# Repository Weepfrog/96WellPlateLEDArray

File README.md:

# 12×8 High-Power 660nm LED Array

A 96-LED (12 across × 8 down, 9 mm pitch) deep-red 660 nm panel with **per-LED
dimming** and **per-LED temperature sensing**, driven by an ESP32 DevKitC.
Designed for JLCPCB fabrication + assembly; all parts chosen from the
JLCPCB/LCSC library (stock verified 2026-07-13).

## System overview

```
24V 4-6A brick ──► CONTROL BOARD ══ 4× 50-way + 1× 20-way IDC ribbon ══► LED BOARD
                   96× PT4115 buck CC        192 anode/cathode lines        96× 660nm 3535 LED
                   6× PCA9685 PWM (I2C)      + analog/logic lines           96× 10k NTC
                   XL1509 5V rail                                           6× CD74HC4067 mux
                   ESP32 DevKitC socket                                     flat back → heatsink
                   3 buttons + status LEDs
```

- **~50 W** total at full drive (≈0.5 W per LED @ 256 mA, huge margin on 3 W-rated LEDs)
- Per-LED PWM: one PT4115 buck constant-current channel per LED, DIM pins on six
  PCA9685 16-channel I2C PWM expanders (run PWM at ~244 Hz → ~10-11 usable bits)
- Per-LED temperature: one 0603 NTC beside each LED, multiplexed 16:1 onto six
  ESP32 ADC1 inputs
- LED board is 4-layer with thermal-via farms; back face is bare copper for a
  bolt-on heatsink (use an insulating thermal pad)

## Repository layout

| Path | What |
|---|---|
| `12x8 Led Array 9mm pitch/` | **LED board** KiCad project (96 LEDs + NTCs + muxes) |
| `control-board/` | **Control board** KiCad project (drivers, PWM, ESP32, UI) |
| `libraries/` | `jlc_parts` symbol/footprint/3D library (converted from EasyEDA, JLCPCB-exact pads) |
| `scripts/design_data.py` | **Single source of truth**: every part, position, and net |
| `scripts/gen_schematics.py` | Regenerates both `.kicad_sch` (parts placed, you wire per CONNECTIONS.md) |
| `scripts/gen_pcbs.py` | Regenerates both `.kicad_pcb` (footprints pre-placed) |
| `reference/datasheets/` | Datasheets for key parts |
| `production/` | JLCPCB BOM + CPL exports |
| `CONNECTIONS.md` | **Your wiring guide** — every net, pin by pin |

## Workflow

1. **Schematics are hierarchical and fully wired**: each board is a root
   sheet + one sub-sheet (`well.kicad_sch` / `channel.kicad_sch`)
   instantiated 96×, with references matching `CONNECTIONS.md` (LED1-96,
   U1-96, …). Verified automatically: KiCad's exported netlist matches the
   intended netlist in `design_data.py` net-for-net; ERC is clean (3 benign
   library-mismatch warnings on the control board). Review, then move to
   layout.
2. Open the PCB — footprints are pre-placed (LED grid at exact 9.0 mm
   pitch; placement still draft). Run **Tools → Update PCB from Schematic
   (F8)**, then route.
3. Regenerating: `python scripts/gen_schematics_hier.py`, then
   `scripts/gen_pcbs.py` with KiCad's Python (see script headers), then
   `python scripts/gen_connections.py`. Verify with
   `scripts/verify_netlist.py` (see header). **Regeneration overwrites the
   sch/pcb files** — don't rerun after manual edits unless you want a reset.

## Key design rules (don't skip)

- **LED polarity:** pad 1 = anode (marked `+` on silk), pad 2 = cathode,
  pad 3 = center thermal pad — **tie pad 3 to pad 2 (cathode)** per Hongli's
  datasheet. Each LED's thermal island is at its own cathode potential, so the
  heatsink must be electrically isolated (thermal pad, not bare paste).
- **PT4115 DIM floats high** = full brightness. Every DIM has a 100k pulldown
  so the panel boots dark. Keep them.
- **One reflow only** for the LEDs (datasheet) — LED board is single-side
  assembly, which satisfies this. Don't hot-air rework casually.
- 24 V power enters each board via its own screw terminal — **do not route
  LED supply current through the IDC ribbons** (they carry per-channel
  anode/cathode pairs and logic only).
- IDC headers and ESP32 sockets are through-hole: hand-solder them (cheaper
  than JLCPCB THT assembly).

## Swapping LED wavelengths

The design is wavelength-agnostic on purpose:

- The 3535 3-pad footprint is the industry-standard pattern (Cree XP
  compatible). 730 nm far-red, 850/940 nm IR, blue, and UV parts from Hongli,
  Silverlight, JNJ and others drop straight in.
- The PT4115 buck **does not care about forward voltage** — anything from
  ~1.5 V (IR) to ~3.4 V (blue/UV) runs at the same regulated current with zero
  component changes.
- Current is set only by the 0.39 Ω sense resistor (256 mA). For a lower-rated
  LED, change R1–R96 on the control board: `I = 0.1 V / Rs`.
- Checklist when swapping: 3535 package with center pad, anode on pad 1 /
  matching polarity, continuous current rating ≥ 300 mA, note the part's own
  reflow limits.
- Mixed arrays are fine too (e.g. 660 nm + 730 nm checkerboard) since every
  channel is independent.

## Firmware map (ESP32 DevKitC-38)

| GPIO | Function |
|---|---|
| 21 / 22 | I2C SDA / SCL → PCA9685 ×6 (0x40–0x45), optional ADS1115 (0x48) |
| 16 / 17 / 18 / 19 | Mux address S0–S3 (shared, all six muxes) |
| 32, 33, 34, 35, 36, 39 | ADC1 inputs ← NTC_SIG1–6 (mux outputs) |
| 25 | Fan PWM (low-side AO3400A) |
| 4 / 13 | Status LED (blue) / Fault LED (red) |
| 14 / 27 / 26 | Buttons MODE / UP / DOWN (to GND, internal pull-ups) |

NTC conversion: 10k NTC (B=3434 K) high side, 10k 1% low side, ratiometric to
3.3 V. Scan all 96 via mux (settle ≥200 µs after address change). Derate any
channel whose pad temperature approaches 85 °C (Hongli's recommended limit).

## Safety

50 W of 660 nm in a 10 cm square is extremely bright — never look at the
array at power, ramp brightness in firmware, and treat the NTC thermal
shutdown as a backstop, not a substitute for the heatsink.

## Status

- [x] Architecture + parts selection (all JLCPCB-stocked, C-numbers in BOM)
- [x] Schematics generated, parts placed with library-verified pinouts
- [ ] PCBs with pre-placed footprints
- [ ] CONNECTIONS.md wiring guide
- [ ] JLCPCB BOM/CPL exports
- [ ] User wiring + routing
- [ ] Order + bring-up

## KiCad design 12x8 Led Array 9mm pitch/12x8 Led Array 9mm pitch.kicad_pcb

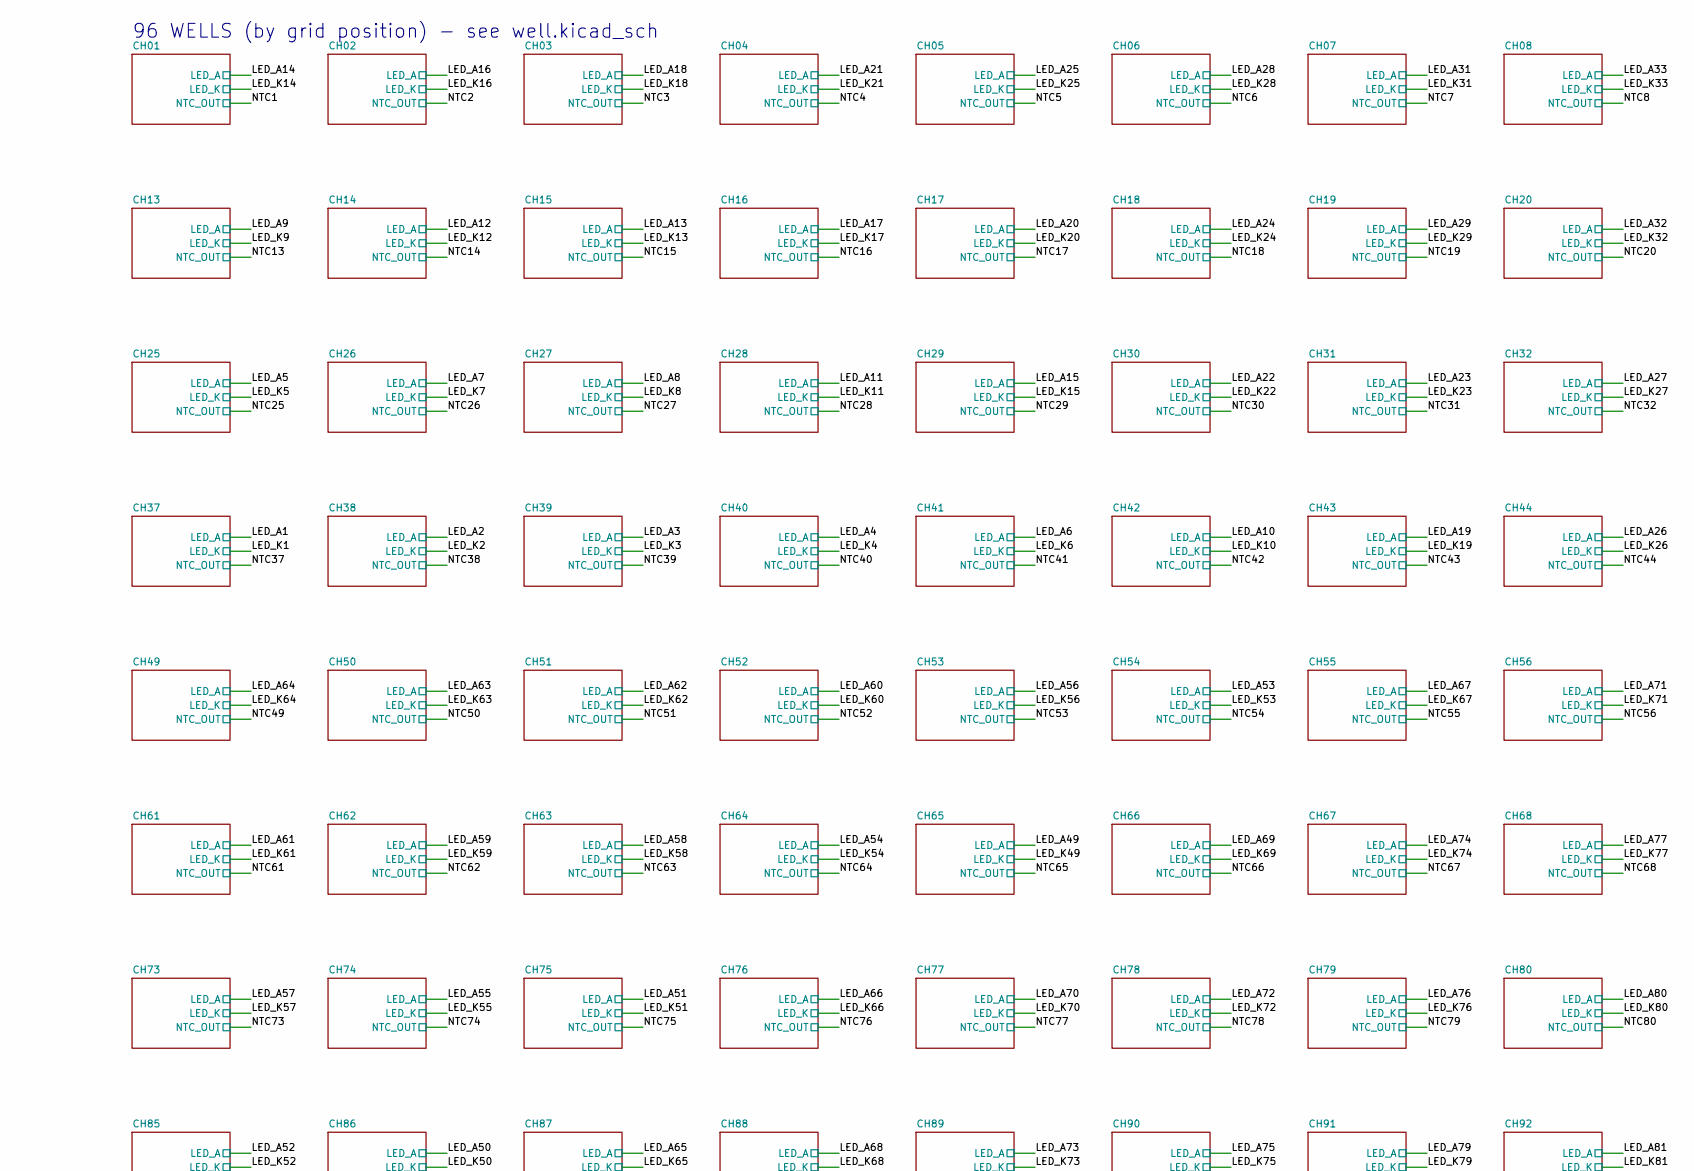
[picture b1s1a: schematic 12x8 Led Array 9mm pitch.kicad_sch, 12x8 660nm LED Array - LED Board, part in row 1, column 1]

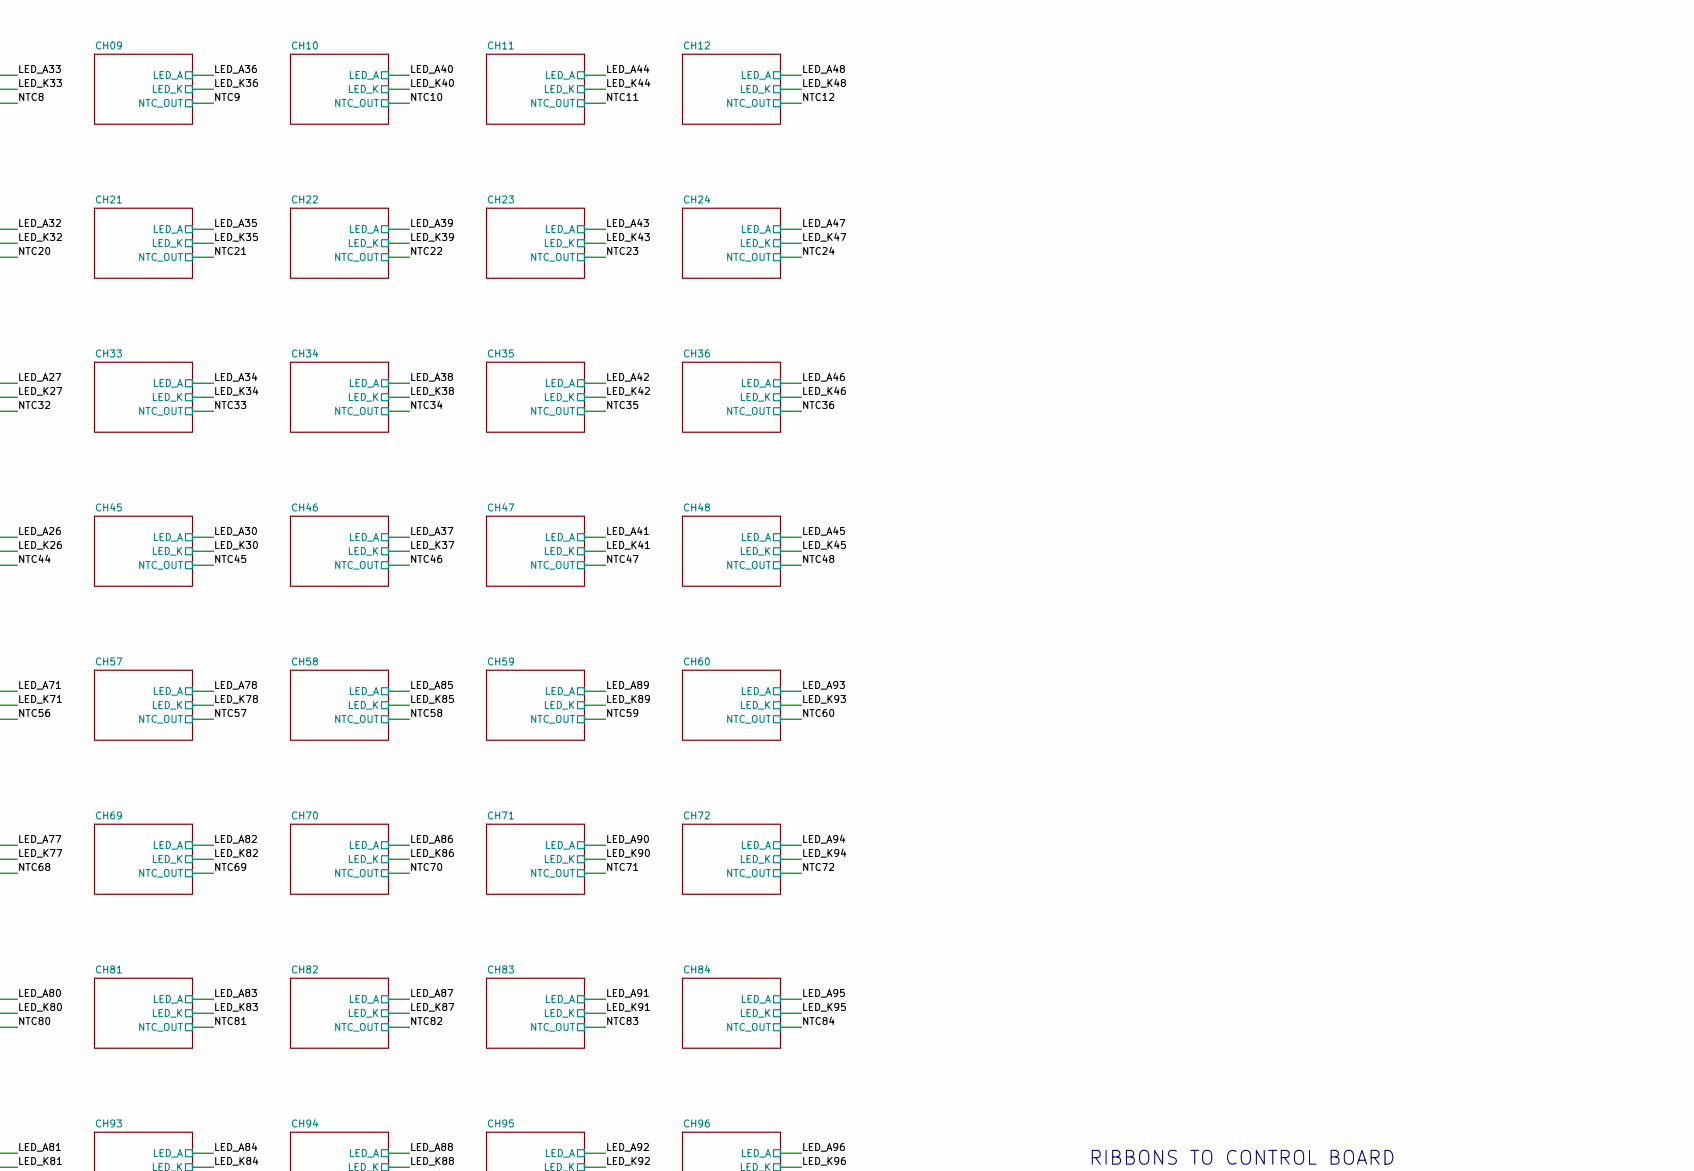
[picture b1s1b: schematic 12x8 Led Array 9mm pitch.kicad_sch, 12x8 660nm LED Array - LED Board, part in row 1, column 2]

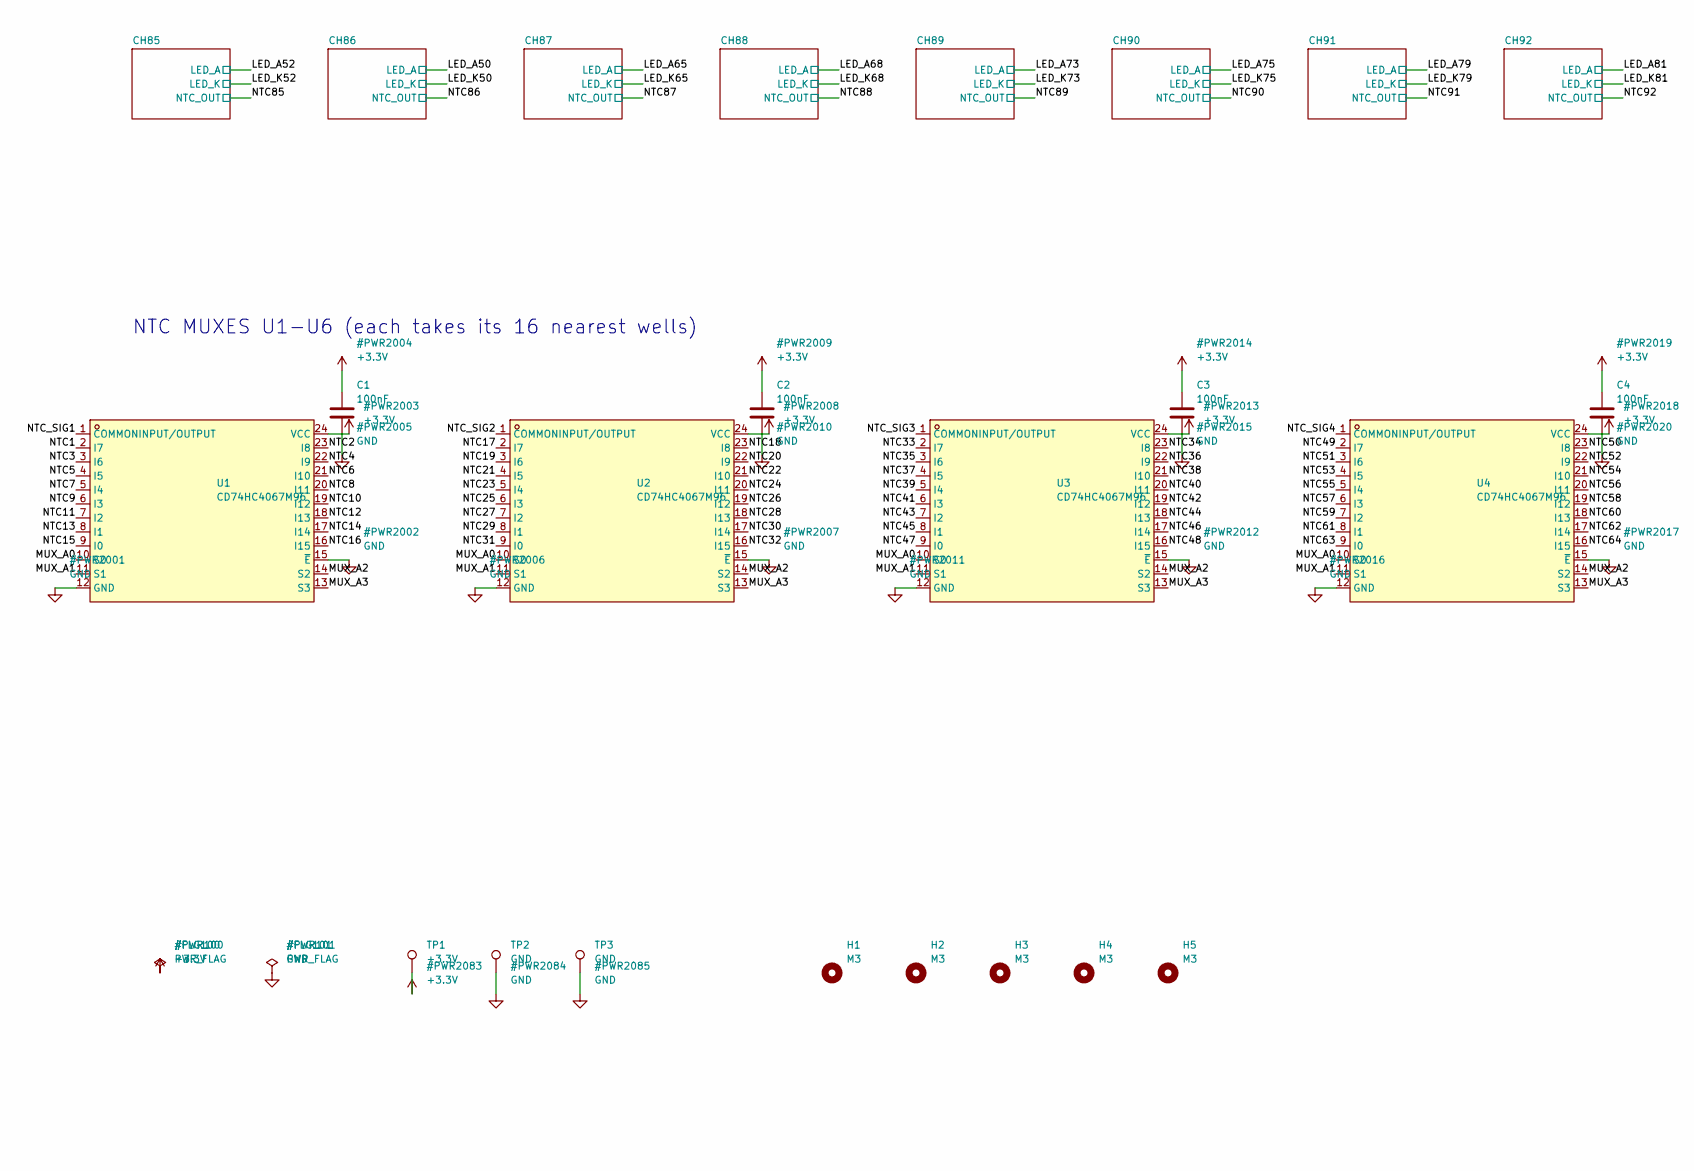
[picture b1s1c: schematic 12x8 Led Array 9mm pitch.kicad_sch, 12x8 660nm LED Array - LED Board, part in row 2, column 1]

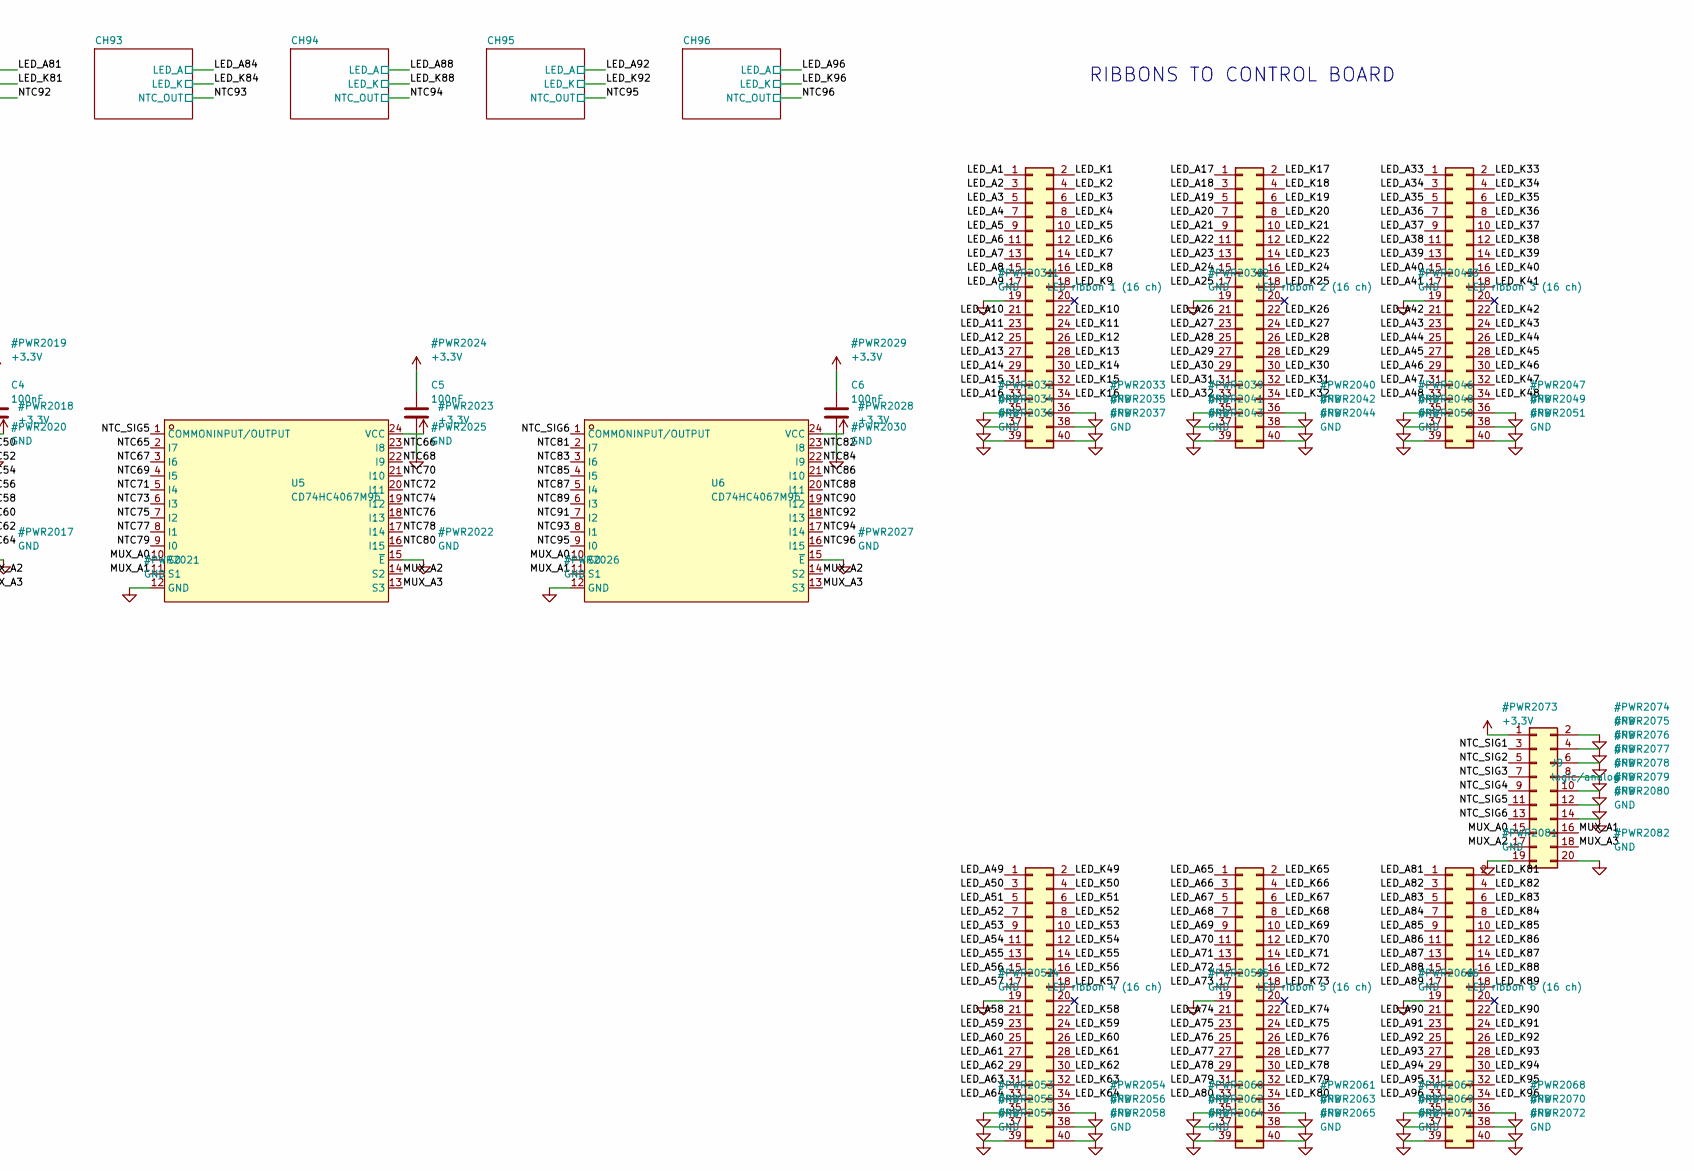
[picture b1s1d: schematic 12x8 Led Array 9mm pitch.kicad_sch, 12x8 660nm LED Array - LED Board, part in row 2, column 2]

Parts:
C1, C2, C3, C4, C5, C6: 100nF; C_0603_1608Metric; LCSC C14663
H1, H2, H3, H4, H5: M3; MountingHole_3.2mm_M3
J1: LED ribbon 1 (16 ch); IDC-Header_2x20_P2.54mm_Vertical; LCSC C9043
J2: LED ribbon 2 (16 ch); IDC-Header_2x20_P2.54mm_Vertical; LCSC C9043
J3: LED ribbon 3 (16 ch); IDC-Header_2x20_P2.54mm_Vertical; LCSC C9043
J4: LED ribbon 4 (16 ch); IDC-Header_2x20_P2.54mm_Vertical; LCSC C9043
J5: LED ribbon 5 (16 ch); IDC-Header_2x20_P2.54mm_Vertical; LCSC C9043
J6: LED ribbon 6 (16 ch); IDC-Header_2x20_P2.54mm_Vertical; LCSC C9043
J9: logic/analog; IDC-Header_2x10_P2.54mm_Horizontal; LCSC C9144
TP1: +3.3V; TestPoint_Pad_1.5x1.5mm
TP2, TP3: GND; TestPoint_Pad_1.5x1.5mm
U1, U2, U3, U4, U5, U6: CD74HC4067M96; SOIC-24_L15.4-W7.5-P1.27-LS10.3-BL; LCSC C496123

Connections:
+3.3V: C1.1, C2.1, C3.1, C4.1, C5.1, C6.1, J9.1, TP1.1 (1_1), U1.24 (VCC), U2.24 (VCC), U3.24 (VCC), U4.24 (VCC), U5.24 (VCC), U6.24 (VCC); also elsewhere on the board
/LED_A1: J1.1; also elsewhere on the board
/LED_A2: J1.3; also elsewhere on the board
/LED_A3: J1.5; also elsewhere on the board
/LED_A4: J1.7; also elsewhere on the board
/LED_A5: J1.9; also elsewhere on the board
/LED_A6: J1.11; also elsewhere on the board
/LED_A7: J1.13; also elsewhere on the board
/LED_A8: J1.15; also elsewhere on the board
/LED_A9: J1.17; also elsewhere on the board
/LED_A10: J1.21; also elsewhere on the board
/LED_A11: J1.23; also elsewhere on the board
/LED_A12: J1.25; also elsewhere on the board
/LED_A13: J1.27; also elsewhere on the board
/LED_A14: J1.29; also elsewhere on the board
/LED_A15: J1.31; also elsewhere on the board
/LED_A16: J1.33; also elsewhere on the board
/LED_A17: J2.1; also elsewhere on the board
/LED_A18: J2.3; also elsewhere on the board
/LED_A19: J2.5; also elsewhere on the board
/LED_A20: J2.7; also elsewhere on the board
/LED_A21: J2.9; also elsewhere on the board
/LED_A22: J2.11; also elsewhere on the board
/LED_A23: J2.13; also elsewhere on the board
/LED_A24: J2.15; also elsewhere on the board
/LED_A25: J2.17; also elsewhere on the board
/LED_A26: J2.21; also elsewhere on the board
/LED_A27: J2.23; also elsewhere on the board
/LED_A28: J2.25; also elsewhere on the board
/LED_A29: J2.27; also elsewhere on the board
/LED_A30: J2.29; also elsewhere on the board
/LED_A31: J2.31; also elsewhere on the board
/LED_A32: J2.33; also elsewhere on the board
/LED_A33: J3.1; also elsewhere on the board
/LED_A34: J3.3; also elsewhere on the board
/LED_A35: J3.5; also elsewhere on the board
/LED_A36: J3.7; also elsewhere on the board
/LED_A37: J3.9; also elsewhere on the board
/LED_A38: J3.11; also elsewhere on the board
/LED_A39: J3.13; also elsewhere on the board
/LED_A40: J3.15; also elsewhere on the board
/LED_A41: J3.17; also elsewhere on the board
/LED_A42: J3.21; also elsewhere on the board
/LED_A43: J3.23; also elsewhere on the board
/LED_A44: J3.25; also elsewhere on the board
/LED_A45: J3.27; also elsewhere on the board
/LED_A46: J3.29; also elsewhere on the board
/LED_A47: J3.31; also elsewhere on the board
/LED_A48: J3.33; also elsewhere on the board
/LED_A49: J4.1; also elsewhere on the board
/LED_A50: J4.3; also elsewhere on the board
/LED_A51: J4.5; also elsewhere on the board
/LED_A52: J4.7; also elsewhere on the board
/LED_A53: J4.9; also elsewhere on the board
/LED_A54: J4.11; also elsewhere on the board
/LED_A55: J4.13; also elsewhere on the board
/LED_A56: J4.15; also elsewhere on the board
/LED_A57: J4.17; also elsewhere on the board
/LED_A58: J4.21; also elsewhere on the board
/LED_A59: J4.23; also elsewhere on the board
/LED_A60: J4.25; also elsewhere on the board
/LED_A61: J4.27; also elsewhere on the board
/LED_A62: J4.29; also elsewhere on the board
/LED_A63: J4.31; also elsewhere on the board
/LED_A64: J4.33; also elsewhere on the board
/LED_A65: J5.1; also elsewhere on the board
/LED_A66: J5.3; also elsewhere on the board
/LED_A67: J5.5; also elsewhere on the board
/LED_A68: J5.7; also elsewhere on the board
/LED_A69: J5.9; also elsewhere on the board
/LED_A70: J5.11; also elsewhere on the board
/LED_A71: J5.13; also elsewhere on the board
/LED_A72: J5.15; also elsewhere on the board
/LED_A73: J5.17; also elsewhere on the board
/LED_A74: J5.21; also elsewhere on the board
/LED_A75: J5.23; also elsewhere on the board
/LED_A76: J5.25; also elsewhere on the board
/LED_A77: J5.27; also elsewhere on the board
/LED_A78: J5.29; also elsewhere on the board
/LED_A79: J5.31; also elsewhere on the board
/LED_A80: J5.33; also elsewhere on the board
/LED_A81: J6.1; also elsewhere on the board
/LED_A82: J6.3; also elsewhere on the board
/LED_A83: J6.5; also elsewhere on the board
/LED_A84: J6.7; also elsewhere on the board
/LED_A85: J6.9; also elsewhere on the board
/LED_A86: J6.11; also elsewhere on the board
/LED_A87: J6.13; also elsewhere on the board
/LED_A88: J6.15; also elsewhere on the board
/LED_A89: J6.17; also elsewhere on the board
/LED_A90: J6.21; also elsewhere on the board
/LED_A91: J6.23; also elsewhere on the board
/LED_A92: J6.25; also elsewhere on the board
/LED_A93: J6.27; also elsewhere on the board
/LED_A94: J6.29; also elsewhere on the board
/LED_A95: J6.31; also elsewhere on the board
/LED_A96: J6.33; also elsewhere on the board
/LED_K1: J1.2; also elsewhere on the board
/LED_K2: J1.4; also elsewhere on the board
/LED_K3: J1.6; also elsewhere on the board
/LED_K4: J1.8; also elsewhere on the board
/LED_K5: J1.10; also elsewhere on the board
/LED_K6: J1.12; also elsewhere on the board
/LED_K7: J1.14; also elsewhere on the board
/LED_K8: J1.16; also elsewhere on the board
/LED_K9: J1.18; also elsewhere on the board
/LED_K10: J1.22; also elsewhere on the board
/LED_K11: J1.24; also elsewhere on the board
/LED_K12: J1.26; also elsewhere on the board
/LED_K13: J1.28; also elsewhere on the board
/LED_K14: J1.30; also elsewhere on the board
/LED_K15: J1.32; also elsewhere on the board
/LED_K16: J1.34; also elsewhere on the board
/LED_K17: J2.2; also elsewhere on the board
/LED_K18: J2.4; also elsewhere on the board
/LED_K19: J2.6; also elsewhere on the board
/LED_K20: J2.8; also elsewhere on the board
/LED_K21: J2.10; also elsewhere on the board
/LED_K22: J2.12; also elsewhere on the board
/LED_K23: J2.14; also elsewhere on the board
/LED_K24: J2.16; also elsewhere on the board
/LED_K25: J2.18; also elsewhere on the board
/LED_K26: J2.22; also elsewhere on the board
/LED_K27: J2.24; also elsewhere on the board
/LED_K28: J2.26; also elsewhere on the board
/LED_K29: J2.28; also elsewhere on the board
/LED_K30: J2.30; also elsewhere on the board
/LED_K31: J2.32; also elsewhere on the board
/LED_K32: J2.34; also elsewhere on the board
/LED_K33: J3.2; also elsewhere on the board
/LED_K34: J3.4; also elsewhere on the board
/LED_K35: J3.6; also elsewhere on the board
/LED_K36: J3.8; also elsewhere on the board
/LED_K37: J3.10; also elsewhere on the board
/LED_K38: J3.12; also elsewhere on the board
/LED_K39: J3.14; also elsewhere on the board
/LED_K40: J3.16; also elsewhere on the board
/LED_K41: J3.18; also elsewhere on the board
/LED_K42: J3.22; also elsewhere on the board
/LED_K43: J3.24; also elsewhere on the board
/LED_K44: J3.26; also elsewhere on the board
/LED_K45: J3.28; also elsewhere on the board
/LED_K46: J3.30; also elsewhere on the board
/LED_K47: J3.32; also elsewhere on the board
/LED_K48: J3.34; also elsewhere on the board
/LED_K49: J4.2; also elsewhere on the board
/LED_K50: J4.4; also elsewhere on the board
/LED_K51: J4.6; also elsewhere on the board
/LED_K52: J4.8; also elsewhere on the board
/LED_K53: J4.10; also elsewhere on the board
/LED_K54: J4.12; also elsewhere on the board
/LED_K55: J4.14; also elsewhere on the board
/LED_K56: J4.16; also elsewhere on the board
/LED_K57: J4.18; also elsewhere on the board
/LED_K58: J4.22; also elsewhere on the board
/LED_K59: J4.24; also elsewhere on the board
/LED_K60: J4.26; also elsewhere on the board
/LED_K61: J4.28; also elsewhere on the board
/LED_K62: J4.30; also elsewhere on the board
/LED_K63: J4.32; also elsewhere on the board
/LED_K64: J4.34; also elsewhere on the board
/LED_K65: J5.2; also elsewhere on the board
/LED_K66: J5.4; also elsewhere on the board
/LED_K67: J5.6; also elsewhere on the board
/LED_K68: J5.8; also elsewhere on the board
/LED_K69: J5.10; also elsewhere on the board
/LED_K70: J5.12; also elsewhere on the board
/LED_K71: J5.14; also elsewhere on the board
/LED_K72: J5.16; also elsewhere on the board
/LED_K73: J5.18; also elsewhere on the board
/LED_K74: J5.22; also elsewhere on the board
/LED_K75: J5.24; also elsewhere on the board
/LED_K76: J5.26; also elsewhere on the board
/LED_K77: J5.28; also elsewhere on the board
/LED_K78: J5.30; also elsewhere on the board
/LED_K79: J5.32; also elsewhere on the board
/LED_K80: J5.34; also elsewhere on the board
/LED_K81: J6.2; also elsewhere on the board
/LED_K82: J6.4; also elsewhere on the board
/LED_K83: J6.6; also elsewhere on the board
/LED_K84: J6.8; also elsewhere on the board
/LED_K85: J6.10; also elsewhere on the board
/LED_K86: J6.12; also elsewhere on the board
/LED_K87: J6.14; also elsewhere on the board
/LED_K88: J6.16; also elsewhere on the board
/LED_K89: J6.18; also elsewhere on the board
/LED_K90: J6.22; also elsewhere on the board
/LED_K91: J6.24; also elsewhere on the board
/LED_K92: J6.26; also elsewhere on the board
/LED_K93: J6.28; also elsewhere on the board
/LED_K94: J6.30; also elsewhere on the board
/LED_K95: J6.32; also elsewhere on the board
/LED_K96: J6.34; also elsewhere on the board
/MUX_A0: J9.15, U1.10 (S0), U2.10 (S0), U3.10 (S0), U4.10 (S0), U5.10 (S0), U6.10 (S0)
/MUX_A1: J9.16, U1.11 (S1), U2.11 (S1), U3.11 (S1), U4.11 (S1), U5.11 (S1), U6.11 (S1)
/MUX_A2: J9.17, U1.14 (S2), U2.14 (S2), U3.14 (S2), U4.14 (S2), U5.14 (S2), U6.14 (S2)
/MUX_A3: J9.18, U1.13 (S3), U2.13 (S3), U3.13 (S3), U4.13 (S3), U5.13 (S3), U6.13 (S3)
/NTC1: U1.2 (I7); also elsewhere on the board
/NTC2: U1.23 (I8); also elsewhere on the board
/NTC3: U1.3 (I6); also elsewhere on the board
/NTC4: U1.22 (I9); also elsewhere on the board
/NTC5: U1.4 (I5); also elsewhere on the board
/NTC6: U1.21 (I10); also elsewhere on the board
/NTC7: U1.5 (I4); also elsewhere on the board
/NTC8: U1.20 (I11); also elsewhere on the board
/NTC9: U1.6 (I3); also elsewhere on the board
/NTC10: U1.19 (I12); also elsewhere on the board
/NTC11: U1.7 (I2); also elsewhere on the board
/NTC12: U1.18 (I13); also elsewhere on the board
/NTC13: U1.8 (I1); also elsewhere on the board
/NTC14: U1.17 (I14); also elsewhere on the board
/NTC15: U1.9 (I0); also elsewhere on the board
/NTC16: U1.16 (I15); also elsewhere on the board
/NTC17: U2.2 (I7); also elsewhere on the board
/NTC18: U2.23 (I8); also elsewhere on the board
/NTC19: U2.3 (I6); also elsewhere on the board
/NTC20: U2.22 (I9); also elsewhere on the board
/NTC21: U2.4 (I5); also elsewhere on the board
/NTC22: U2.21 (I10); also elsewhere on the board
/NTC23: U2.5 (I4); also elsewhere on the board
/NTC24: U2.20 (I11); also elsewhere on the board
/NTC25: U2.6 (I3); also elsewhere on the board
/NTC26: U2.19 (I12); also elsewhere on the board
/NTC27: U2.7 (I2); also elsewhere on the board
/NTC28: U2.18 (I13); also elsewhere on the board
/NTC29: U2.8 (I1); also elsewhere on the board
/NTC30: U2.17 (I14); also elsewhere on the board
/NTC31: U2.9 (I0); also elsewhere on the board
/NTC32: U2.16 (I15); also elsewhere on the board
/NTC33: U3.2 (I7); also elsewhere on the board
/NTC34: U3.23 (I8); also elsewhere on the board
/NTC35: U3.3 (I6); also elsewhere on the board
/NTC36: U3.22 (I9); also elsewhere on the board
/NTC37: U3.4 (I5); also elsewhere on the board
/NTC38: U3.21 (I10); also elsewhere on the board
/NTC39: U3.5 (I4); also elsewhere on the board
/NTC40: U3.20 (I11); also elsewhere on the board
/NTC41: U3.6 (I3); also elsewhere on the board
/NTC42: U3.19 (I12); also elsewhere on the board
/NTC43: U3.7 (I2); also elsewhere on the board
/NTC44: U3.18 (I13); also elsewhere on the board
/NTC45: U3.8 (I1); also elsewhere on the board
/NTC46: U3.17 (I14); also elsewhere on the board
/NTC47: U3.9 (I0); also elsewhere on the board
/NTC48: U3.16 (I15); also elsewhere on the board
/NTC49: U4.2 (I7); also elsewhere on the board
/NTC50: U4.23 (I8); also elsewhere on the board
/NTC51: U4.3 (I6); also elsewhere on the board
/NTC52: U4.22 (I9); also elsewhere on the board
/NTC53: U4.4 (I5); also elsewhere on the board
/NTC54: U4.21 (I10); also elsewhere on the board
/NTC55: U4.5 (I4); also elsewhere on the board
/NTC56: U4.20 (I11); also elsewhere on the board
/NTC57: U4.6 (I3); also elsewhere on the board
/NTC58: U4.19 (I12); also elsewhere on the board
/NTC59: U4.7 (I2); also elsewhere on the board
/NTC60: U4.18 (I13); also elsewhere on the board
/NTC61: U4.8 (I1); also elsewhere on the board
/NTC62: U4.17 (I14); also elsewhere on the board
/NTC63: U4.9 (I0); also elsewhere on the board
/NTC64: U4.16 (I15); also elsewhere on the board
/NTC65: U5.2 (I7); also elsewhere on the board
/NTC66: U5.23 (I8); also elsewhere on the board
/NTC67: U5.3 (I6); also elsewhere on the board
/NTC68: U5.22 (I9); also elsewhere on the board
/NTC69: U5.4 (I5); also elsewhere on the board
/NTC70: U5.21 (I10); also elsewhere on the board
/NTC71: U5.5 (I4); also elsewhere on the board
/NTC72: U5.20 (I11); also elsewhere on the board
/NTC73: U5.6 (I3); also elsewhere on the board
/NTC74: U5.19 (I12); also elsewhere on the board
/NTC75: U5.7 (I2); also elsewhere on the board
/NTC76: U5.18 (I13); also elsewhere on the board
/NTC77: U5.8 (I1); also elsewhere on the board
/NTC78: U5.17 (I14); also elsewhere on the board
/NTC79: U5.9 (I0); also elsewhere on the board
/NTC80: U5.16 (I15); also elsewhere on the board
/NTC81: U6.2 (I7); also elsewhere on the board
/NTC82: U6.23 (I8); also elsewhere on the board
/NTC83: U6.3 (I6); also elsewhere on the board
/NTC84: U6.22 (I9); also elsewhere on the board
/NTC85: U6.4 (I5); also elsewhere on the board
/NTC86: U6.21 (I10); also elsewhere on the board
/NTC87: U6.5 (I4); also elsewhere on the board
/NTC88: U6.20 (I11); also elsewhere on the board
/NTC89: U6.6 (I3); also elsewhere on the board
/NTC90: U6.19 (I12); also elsewhere on the board
/NTC91: U6.7 (I2); also elsewhere on the board
/NTC92: U6.18 (I13); also elsewhere on the board
/NTC93: U6.8 (I1); also elsewhere on the board
/NTC94: U6.17 (I14); also elsewhere on the board
/NTC95: U6.9 (I0); also elsewhere on the board
/NTC96: U6.16 (I15); also elsewhere on the board
/NTC_SIG1: J9.3, U1.1 (COMMONINPUT/OUTPUT)
/NTC_SIG2: J9.5, U2.1 (COMMONINPUT/OUTPUT)
/NTC_SIG3: J9.7, U3.1 (COMMONINPUT/OUTPUT)
/NTC_SIG4: J9.9, U4.1 (COMMONINPUT/OUTPUT)
/NTC_SIG5: J9.11, U5.1 (COMMONINPUT/OUTPUT)
/NTC_SIG6: J9.13, U6.1 (COMMONINPUT/OUTPUT)
GND: C1.2, C2.2, C3.2, C4.2, C5.2, C6.2, J1.19, J1.35, J1.36, J1.37, J1.38, J1.39, J1.40, J2.19, J2.35, J2.36, J2.37, J2.38, J2.39, J2.40, J3.19, J3.35, J3.36, J3.37, J3.38, J3.39, J3.40, J4.19, J4.35, J4.36, J4.37, J4.38, J4.39, J4.40, J5.19, J5.35, J5.36, J5.37, J5.38, J5.39, J5.40, J6.19, J6.35, J6.36, J6.37, J6.38, J6.39, J6.40, J9.2, J9.4, J9.6, J9.8, J9.10, J9.12, J9.14, J9.19, J9.20, TP2.1 (1_1), TP3.1 (1_1), U1.12 (GND), U1.15 (~E), U2.12 (GND), U2.15 (~E), U3.12 (GND), U3.15 (~E), U4.12 (GND), U4.15 (~E), U5.12 (GND), U5.15 (~E), U6.12 (GND), U6.15 (~E); also elsewhere on the board

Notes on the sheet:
96 WELLS (by grid position) - see well.kicad_sch
NTC MUXES U1-U6 (each takes its 16 nearest wells)
RIBBONS TO CONTROL BOARD
